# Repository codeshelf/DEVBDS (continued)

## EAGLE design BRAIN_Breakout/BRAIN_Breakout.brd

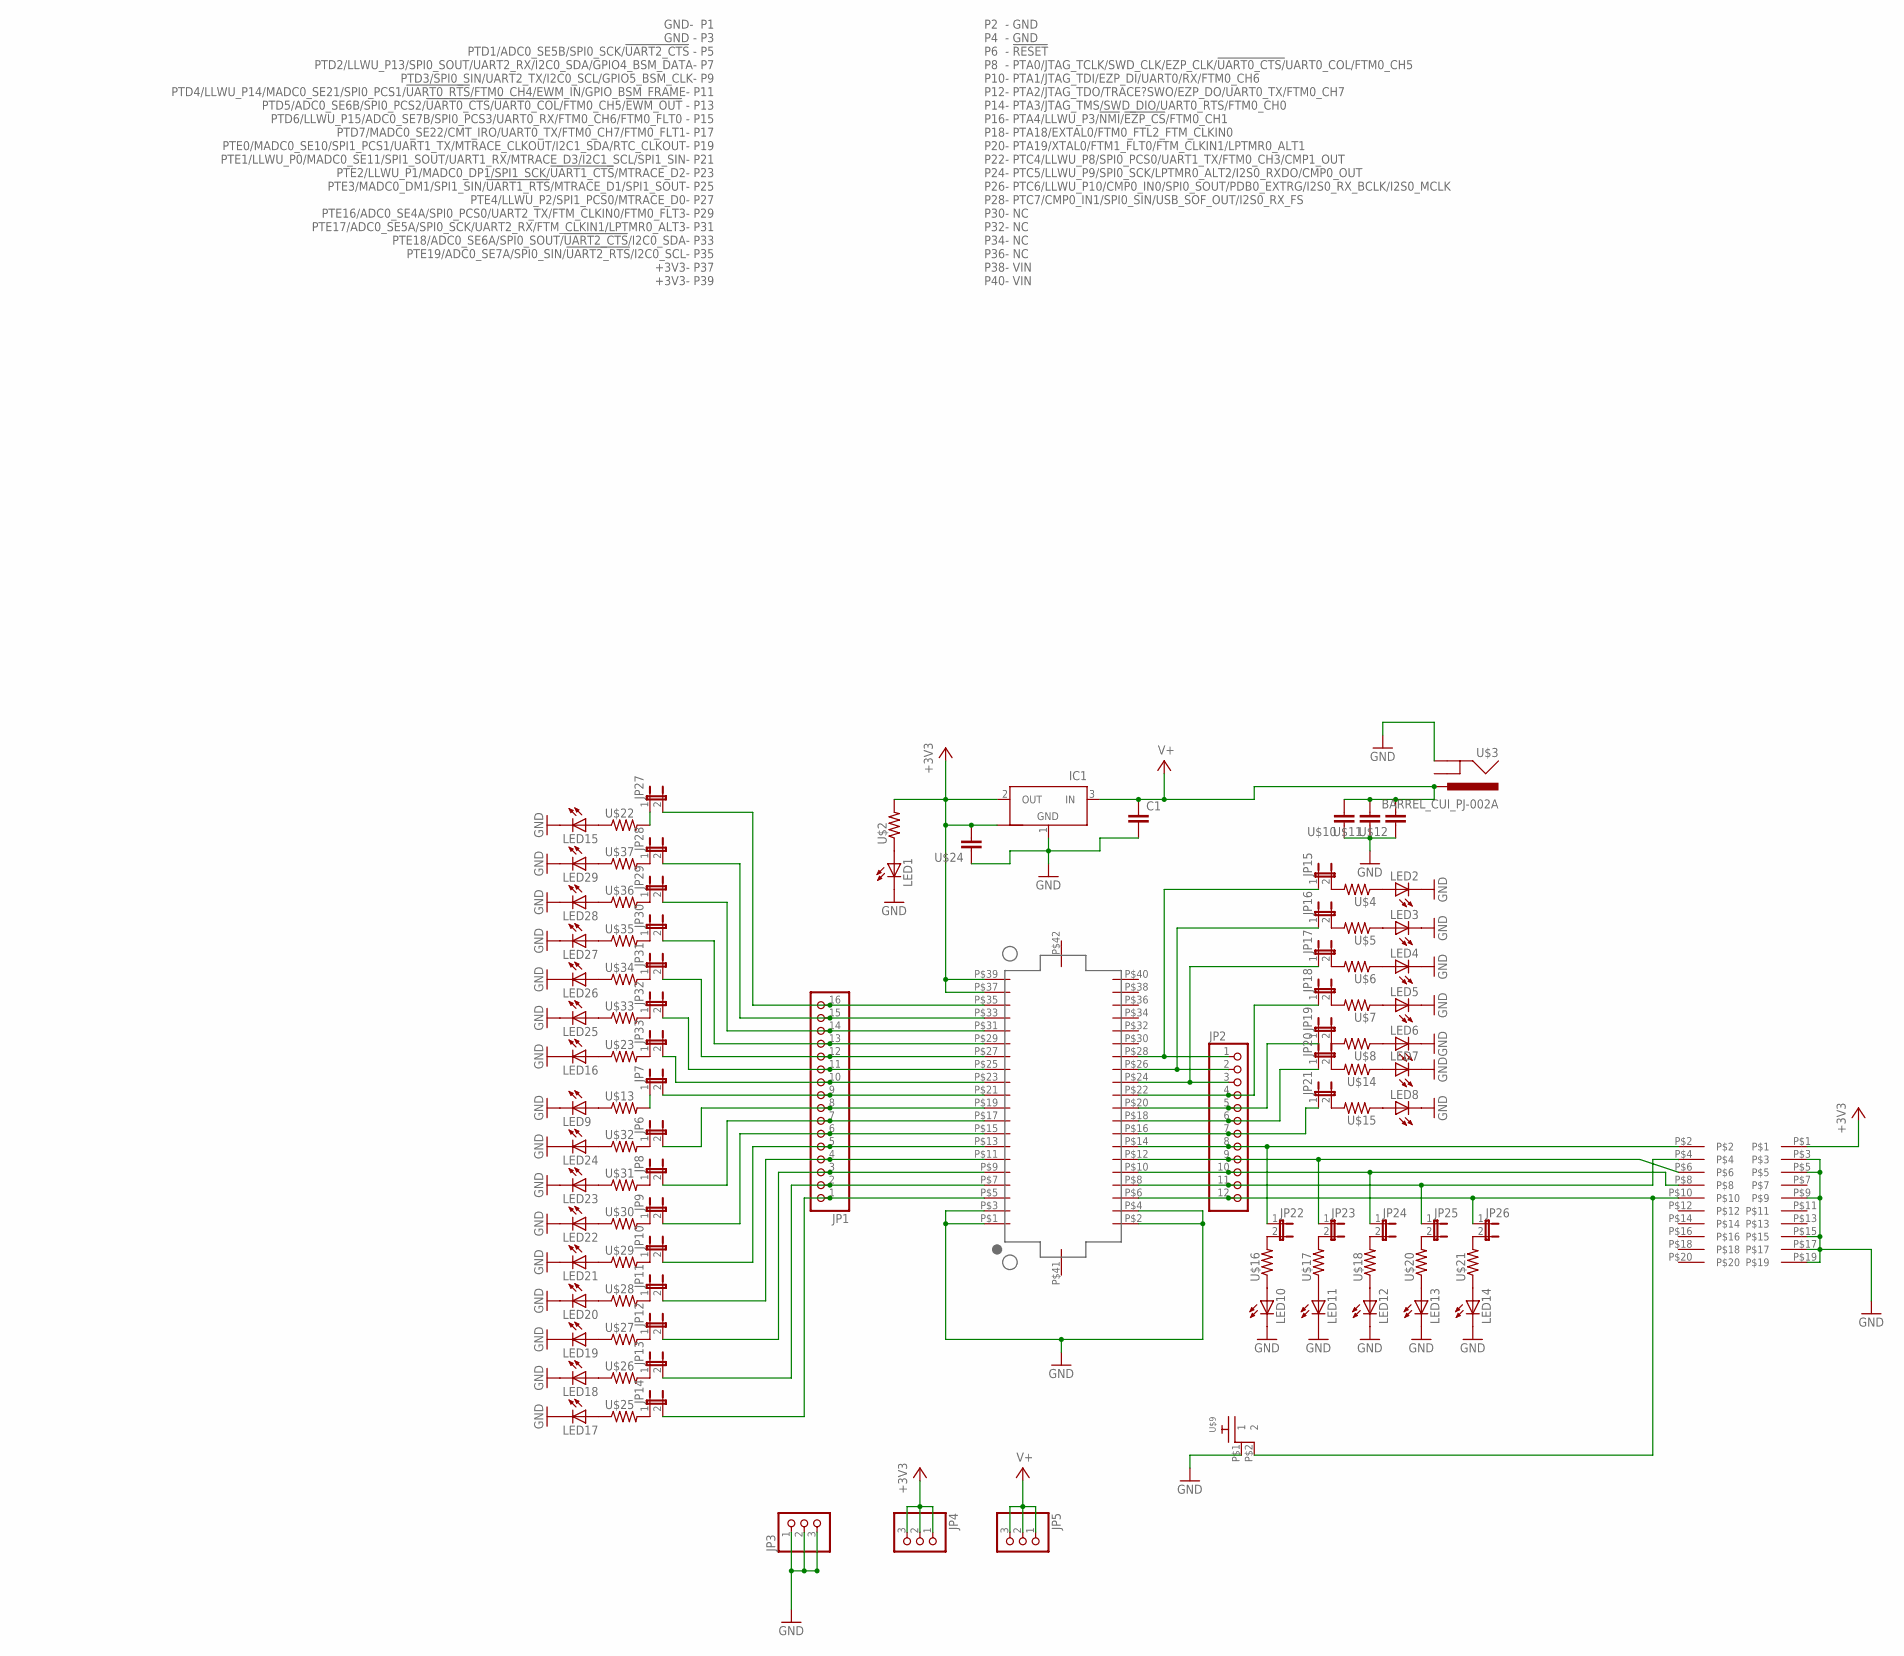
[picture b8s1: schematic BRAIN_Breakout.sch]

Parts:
C1: RF-C0805; C0805
IC1: NCP1117ST33T3G_1; SOT223
JP1: PINHD-1X16; 1X16
JP2: PINHD-1X12; 1X12
JP3, JP4, JP5: PINHD-1X3; 1X03
JP6, JP7, JP8, JP9, JP10, JP11, JP12, JP13, JP14, JP15, JP16, JP17, JP18, JP19, JP20, JP21, JP22, JP23, JP24, JP25, JP26, JP27, JP28, JP29, JP30, JP31, JP32, JP33: JUMPER-2SMD-NO-NS; SJ_2S-NO-NS
LED1, LED2, LED3, LED4, LED5, LED6, LED7, LED8, LED9, LED10, LED11, LED12, LED13, LED14, LED15, LED16, LED17, LED18, LED19, LED20, LED21, LED22, LED23, LED24, LED25, LED26, LED27, LED28, LED29: LEDCHIP-LED0805; CHIP-LED0805
U$1: DF12_F
U$2, U$4, U$5, U$6, U$7, U$8, U$13, U$14, U$15, U$16, U$17, U$18, U$20, U$21, U$22, U$23, U$25, U$26, U$27, U$28, U$29, U$30, U$31, U$32, U$33, U$34, U$35, U$36, U$37: RF-R0805; RF-C0805
U$3: BARREL_CUI_PJ-002A
U$9: RA_BUTTON
U$10, U$11, U$12, U$24: RF-C0805; C0805
U$19: 2X10JTAG

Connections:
+3V3: IC1.2 (OUT), IC1.4 (OUT1), JP4.1, JP4.2, JP4.3, U$1.P$37 (+3V3), U$1.P$39 (+3V3), U$2.2, U$19.P$1, U$24.2
GND: C1.2, IC1.1 (GND), JP3.1, JP3.2, JP3.3, LED1.C, LED2.C, LED3.C, LED4.C, LED5.C, LED6.C, LED7.C, LED8.C, LED9.C, LED10.C, LED11.C, LED12.C, LED13.C, LED14.C, LED15.C, LED16.C, LED17.C, LED18.C, LED19.C, LED20.C, LED21.C, LED22.C, LED23.C, LED24.C, LED25.C, LED26.C, LED27.C, LED28.C, LED29.C, U$1.P$1 (GND), U$1.P$2 (GND), U$1.P$3 (GND), U$1.P$4 (GND), U$3.P$2 (GND), U$9.P$1 (1), U$10.1, U$11.1, U$12.1, U$19.P$3, U$19.P$5, U$19.P$9, U$19.P$15, U$19.P$17, U$19.P$19, U$24.1
unnamed: LED1.A, U$2.1
unnamed: LED2.A, U$4.1
unnamed: LED3.A, U$5.1
unnamed: LED4.A, U$6.1
unnamed: LED8.A, U$15.1
unnamed: LED5.A, U$7.1
unnamed: LED6.A, U$8.1
unnamed: LED7.A, U$14.1
unnamed: LED9.A, U$13.1
unnamed: JP7.1, U$13.2
unnamed: JP21.2, U$15.2
unnamed: JP20.2, U$14.2
unnamed: JP19.2, U$8.2
unnamed: JP18.2, U$7.2
unnamed: JP17.2, U$6.2
unnamed: JP16.2, U$5.2
unnamed: JP15.2, U$4.2
unnamed: JP6.1, U$32.2
unnamed: JP8.1, U$31.2
unnamed: JP9.1, U$30.2
unnamed: JP2.1, JP15.1, U$1.P$28 (PTC7/CMP0_IN1/SPI0_SIN/USB_SOF_OUT/I2S0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)
unnamed: JP2.2, JP16.1, U$1.P$26 (PTC6/LLWU_P10/CMP0_IN0/SPI0_SOUT/PDB0_E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)
unnamed: JP2.3, JP17.1, U$1.P$24 (PTC5/LLWU_P8/SPI0_PCS0/UART1_TX/FTM0_CH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)
unnamed: JP2.4, JP18.1, U$1.P$22 (PTC4/LLWU_P8/SPI0_PCS0/UART1_TX/FTM0_CH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)
unnamed: JP2.5, JP19.1, U$1.P$20 (PTA19/XTAL0/FTM1_FLT0/FTM_CLKIN1/LPTMR0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)
unnamed: JP2.6, JP20.1, U$1.P$18 (PTA18/EXTAL0/FTM0_FTL2_FTM_CLKIN0)
unnamed: JP2.7, JP21.1, U$1.P$16 (PTA4/LLWU_P3/!NMI!/!EZP_CS!/FTM0_CH1)
unnamed: LED15.A, U$22.1
unnamed: LED17.A, U$25.1
unnamed: LED18.A, U$26.1
unnamed: LED19.A, U$27.1
unnamed: LED20.A, U$28.1
unnamed: LED16.A, U$23.1
unnamed: LED25.A, U$33.1
unnamed: LED26.A, U$34.1
unnamed: LED27.A, U$35.1
unnamed: LED21.A, U$29.1
unnamed: LED22.A, U$30.1
unnamed: LED23.A, U$31.1
unnamed: LED24.A, U$32.1
unnamed: JP10.1, U$29.2
unnamed: JP11.1, U$28.2
unnamed: JP14.1, U$25.2
unnamed: JP13.1, U$26.2
unnamed: JP12.1, U$27.2
unnamed: LED28.A, U$36.1
unnamed: JP2.8, JP22.1, U$1.P$14 (PTA3/JTAG_TMS/SWD_DIO/UART0_RTS/FTM0_CH0), U$19.P$2
unnamed: LED10.A, U$16.1
unnamed: JP22.2, U$16.2
unnamed: JP2.9, JP23.1, U$1.P$12 (PTA2/JTAG_TDO/TRACE?SWO/EZP_DO/UART0_TX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), U$19.P$6
unnamed: LED11.A, U$17.1
unnamed: JP23.2, U$17.2
unnamed: JP2.10, JP24.1, U$1.P$10 (PTA1/JTAG_TDI/EZP_DI/UART0/RX/FTM0_CH6), U$19.P$8
unnamed: LED12.A, U$18.1
unnamed: JP24.2, U$18.2
unnamed: JP2.11, JP25.1, U$1.P$8 (PTA0/JTAG_TCLK/SWD_CLK/EZP_CLK/!UART0_C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), U$19.P$4
unnamed: LED13.A, U$20.1
unnamed: JP25.2, U$20.2
unnamed: JP2.12, JP26.1, U$1.P$6 (!RESET), U$9.P$2 (2), U$19.P$10
unnamed: LED14.A, U$21.1
unnamed: JP26.2, U$21.2
unnamed: LED29.A, U$37.1
unnamed: JP27.1, U$22.2
unnamed: JP28.1, U$37.2
unnamed: JP29.1, U$36.2
unnamed: JP30.1, U$35.2
unnamed: JP31.1, U$34.2
unnamed: JP32.1, U$33.2
unnamed: JP33.1, U$23.2
PTD1: JP1.1, JP14.2, U$1.P$5 (PTD1/ADC0_SE5B/SPI0_SCK/!UART2_CTS)
PTD2: JP1.2, JP13.2, U$1.P$7 (PTD2/LLWU_P13/SPI0_SOUT/UART2_RX/I2C0_S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)
PTD3: JP1.3, JP12.2, U$1.P$9 (PTD3/SPI0_SIN/UART2_TX/I2C0_SCL/GPIO5_B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)
PTD4: JP1.4, JP11.2, U$1.P$11 (PTD4/LLWU_P14/MADC0_SE21/SPI0_PCS1/!UAR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)
PTD5: JP1.5, JP10.2, U$1.P$13 (PTD5/ADC0_SE6B/SPI0_PCS2/!UART0_CTS!/!U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)
PTD6: JP1.6, JP9.2, U$1.P$15 (PTD6/LLWU_P15/ADC0_SE7B/SPI0_PCS3/UART0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)
PTD7: JP1.7, JP8.2, U$1.P$17 (PTD7/MADC0_SE22/CMT_IRO/UART0_TX/FTM0_C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)
PTE0: JP1.8, JP6.2, U$1.P$19 (PTE0/MADC0_SE10/SPI1_PCS1/UART1_TX/MTRA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)
PTE1: JP1.9, JP7.2, U$1.P$21 (PTE1/LLWU_P0/MADC0_SE11/SPI1_SOUT/UART1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)
PTE2: JP1.10, JP33.2, U$1.P$23 (PTE2/LLWU_P1/MADC0_DP1/SPI1_SCK/!UART1_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)
PTE3: JP1.11, JP32.2, U$1.P$25 (PTE3/MADC0_DM1/SPI1_SIN/!UART1_RTS!/MTR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)
PTE4: JP1.12, JP31.2, U$1.P$27 (PTE4/LLWU_P2/SPI1_PCS0/MTRACE_D0)
PTE16: JP1.13, JP30.2, U$1.P$29 (PTE16/ADC0_SE4A/SPI0_PCS0/UART2_TX/FTM_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)
PTE17: JP1.14, JP29.2, U$1.P$31 (PTE17/ADC0_SE5A/SPI0_SCK/UART2_RX/FTM_C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)
PTE18: JP1.15, JP28.2, U$1.P$33 (PTE18/ADC0_SE6A/SPI0_SOUT/!UART2_CTS!/I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)
PTE19: JP1.16, JP27.2, U$1.P$35 (PTE19/ADC0_SE7A/SPI0_SIN/!UART2_RTS!/I2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)
V+: C1.1, IC1.3 (IN), JP5.1, JP5.2, JP5.3, U$3.P$1 (PWR), U$10.2, U$11.2, U$12.2

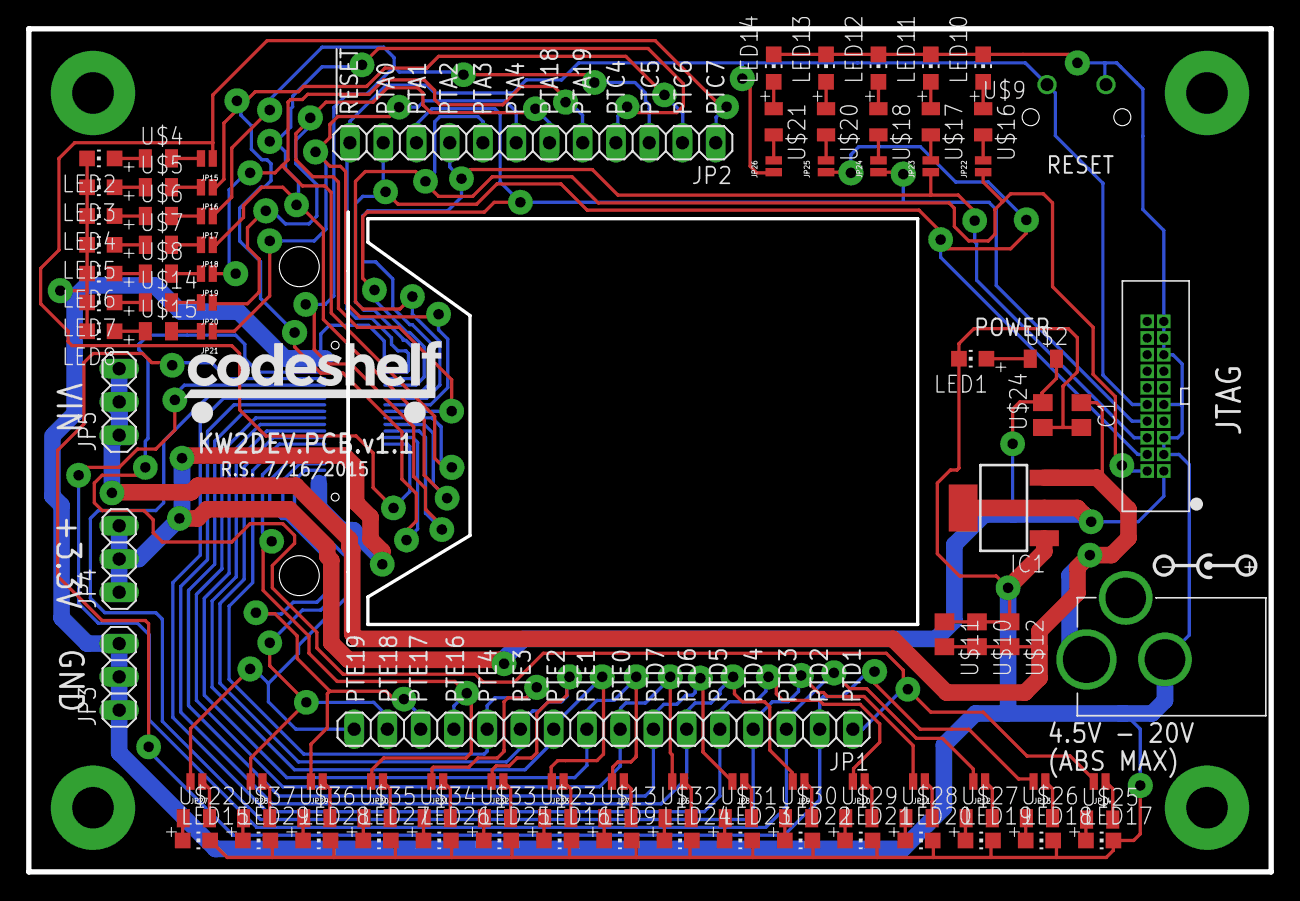
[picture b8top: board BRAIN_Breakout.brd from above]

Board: 2 copper layers, 94.9 x 64.4 mm, 101 parts (1 on the bottom side), 88 nets.

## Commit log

2015-05-15 Added some things
2015-05-30 Updated BRAIN Breakout with silkscreen
    Added silkscreen fixes for production run
2015-07-16 Commit board w/switches & fixes (updated to v1.1)
    Hadn't previousy committed produced board (includes Gerbers). Just fixed
    JTAG and RESET button ground traces and incremented date + version to
    1.1 and 7/16
2015-07-31 Added board for new KW2
2016-01-08 Ignore *.b## files
2016-01-08 sync repo
    Get the DEVBDS work in sync
2016-01-08 Change the FTDI-JTAG debug board
    * Now has built-in pull up/down resistors.
    * 4-layer board
    * Cleaned up, and has ground planes.
2016-01-12 Make the JTAG board more complex for the shop
    Chris asked that the 4-layer board be more complex to help with
    testing. Also added a DRD drill file.
2016-01-12 CAM files for first test board
    First .cam and LMD files for cutting test board
2016-01-13 Change the FTDI-JTAG vias to 0.25mm
    Chris asked for this.
2016-01-13 Revised cam files
    .2 vias and both boards programmed for 4-layer prototype
2016-01-15 Added USB_SWD Test board
    Piece of new CHE, will also be a useful USB programmer.
2016-01-18 Misc changes (SWD)
    Misc changes (SWD)
2016-01-21 Applied new design rules
2016-01-25 Change the FTDI-JTAG test adapter to match the new CS DRU.
2016-01-28 Messing w/ Programmer
    Tweaking USB
2016-02-03 Redo the JTAG mini header to be SMD
2016-03-08 Create an IR LED dev board
2016-03-08 Added holes to the LED jig
